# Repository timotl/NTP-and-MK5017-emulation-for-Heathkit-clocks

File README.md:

# NTP-and-MK5017-emulation-for-Heathkit-clocks
Documentation and modification of original clock to use ESP32 module instead of MK5017. 
Uses original chip socket and only requires 5v power module. 
No additional changes to the original hardware. 
Includes schematic and PCB for interface board. 
Full code and description of function. 
Documentation of the MK5017 

ESP32 sketch to replace MK5017AA and BA used in HeathKit panaplex clocks
Requires shift register and level shifting interface which connects to the original board via chip socket
No modifications to the original clock, except adding a 5v power supply module at the 120v input line
Heathkit GC-1092D, Heathkit GC-1005, Heathkit GC-1092A, Heathkit GC-1094 all fully tested
Display updates are state driven and writing to display is handled by hardware timer

WIFI mode:
Portal will be active if the configured wifi settings do not connect or if the time cannot be set from the configured NTP server after 1 minute.
NTP server, timezone, display off times are set through the portal.

ESP Touch (also snooze or alarmoff switches) changes display from Time to Date, Date to display off, display off to on.
GC-1092A/D - Original 555 touch hardware can be used, however each touch event must be at least 5 seconds apart.

MK5017 mode:
Switches and all behavior faithful to original hardware
RTC simulates battery backup of the GC-1092A/D (but works on all models) - Will consider time valid for configurable number of hours.
Note: some RTC modules don't keep time when powered off. Set BatteryBackup to 0 to disable holdover.
Switching modes will reset the model. Set model by pressing Hour/Month switch until the correct model is displayed, then toggle Time Set.

Switching modes:
Holding Hour/Month switch at power up will change between MK5017 and Wifi mode. Display will go from 888888 to ------ and restart

ArduinoOTA mode:
Alarm/Date switch also enters OTA mode. OTA mode uses AP mode with password and times out after 10 min.

Troubleshooting - Toggle Time Set switch 3x in under 5 seconds.
WIFI mode: Restart to portal to adjust WIFI and NTP settings.
MK5017 mode: Restart clearing RTC and model

Select ESP32-WROOM-DA Module in Arduino IDE
Partition scheme "Minimal SPIFFS (1.9MB APP with OTA/190KB SPIFFS) required if SerialBT is enabled

Also includes Manuals and other datasheets for the various models I can find.

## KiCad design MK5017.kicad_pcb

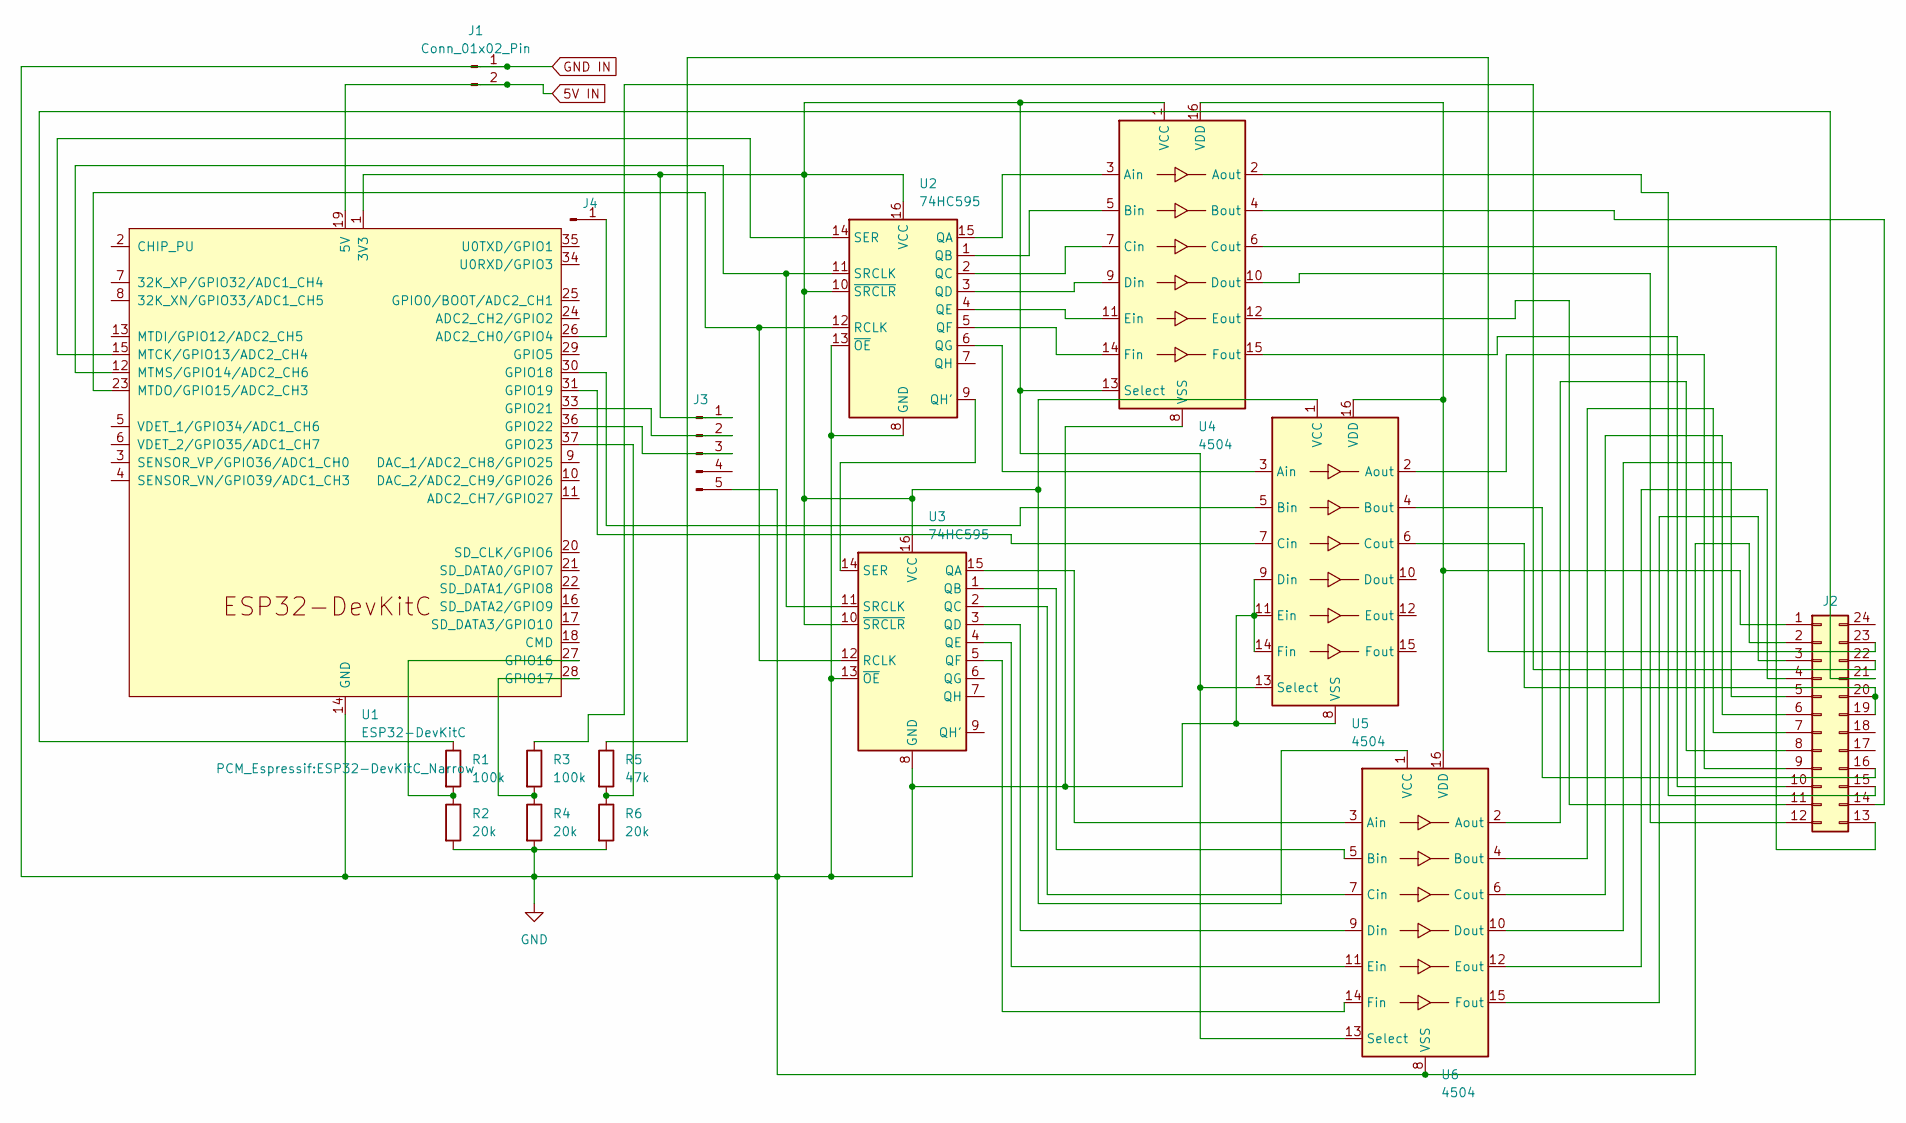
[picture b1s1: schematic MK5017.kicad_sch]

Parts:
J1: Conn_01x02_Pin; JST_EH_B2B-EH-A_1x02_P2.50mm_Vertical
J2: IDC-Header_2x12_P2.54mm_Vertical
J3: Conn_01x05_Pin; PinHeader_1x05_P2.54mm_Vertical
J4: Conn_01x01_Pin; PinHeader_1x01_P2.54mm_Vertical
R1, R3: 100k; R_0603_1608Metric
R2, R4, R6: 20k; R_0603_1608Metric
R5: 47k; R_0603_1608Metric
U1: ESP32-DevKitC; ESP32-DevKitC_Narrow
U2, U3: 74HC595; TSSOP-16_4.4x5mm_P0.65mm
U4, U5, U6: 4504; TSSOP-16_4.4x5mm_P0.65mm

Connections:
5V IN: J1.2, U1.19 (5V); also elsewhere on the board
GND IN: J1.1, J2.2, J3.5, R2.2, R4.2, R6.2, U1.14 (GND), U1.32 (GND), U1.38 (GND), U2.8 (GND), U2.13 (~OE), U3.8 (GND), U3.13 (~OE), U4.8 (VSS), U5.8 (VSS), U5.9 (Din), U5.11 (Ein), U5.14 (Fin), U6.8 (VSS); also elsewhere on the board
unnamed: J2.1, U4.16 (VDD), U5.16 (VDD), U6.16 (VDD)
unnamed: J2.3, U6.15 (Fout)
unnamed: J2.4, U6.12 (Eout)
unnamed: J2.5, U6.10 (Dout)
unnamed: J2.6, U6.6 (Cout)
unnamed: J2.7, U6.4 (Bout)
unnamed: J2.8, U6.2 (Aout)
unnamed: J2.9, U5.2 (Aout)
unnamed: J2.10, U4.15 (Fout)
unnamed: J2.11, U4.12 (Eout)
unnamed: J2.12, U4.10 (Dout)
unnamed: J2.13, U4.6 (Cout)
unnamed: J2.14, U4.4 (Bout)
unnamed: J2.15, U4.2 (Aout)
unnamed: J2.16, U5.4 (Bout)
unnamed: J2.19, J2.20, U5.6 (Cout)
unnamed: J2.21, R1.1
unnamed: J2.22, R3.1
unnamed: J2.23, R5.1
unnamed: J3.1, U1.1 (3V3), U2.10 (~SRCLR), U2.16 (VCC), U3.10 (~SRCLR), U3.16 (VCC), U4.1 (VCC), U4.13 (Select), U5.1 (VCC), U5.13 (Select), U6.1 (VCC), U6.13 (Select)
unnamed: J3.2, U1.33 (GPIO21)
unnamed: J3.3, U1.36 (GPIO22)
unnamed: J4.1, U1.26 (ADC2_CH0/GPIO4)
unnamed: R1.2, R2.1, U1.27 (GPIO16)
unnamed: R3.2, R4.1, U1.28 (GPIO17)
unnamed: U1.30 (GPIO18), U5.5 (Bin)
unnamed: U1.31 (GPIO19), U5.7 (Cin)
unnamed: R5.2, R6.1, U1.37 (GPIO23)
unnamed: U1.15 (MTCK/GPIO13/ADC2_CH4), U2.14 (SER)
unnamed: U1.23 (MTDO/GPIO15/ADC2_CH3), U2.12 (RCLK), U3.12 (RCLK)
unnamed: U1.12 (MTMS/GPIO14/ADC2_CH6), U2.11 (SRCLK), U3.11 (SRCLK)
unnamed: U2.15 (QA), U4.3 (Ain)
unnamed: U2.1 (QB), U4.5 (Bin)
unnamed: U2.2 (QC), U4.7 (Cin)
unnamed: U2.3 (QD), U4.9 (Din)
unnamed: U2.4 (QE), U4.11 (Ein)
unnamed: U2.5 (QF), U4.14 (Fin)
unnamed: U2.6 (QG), U5.3 (Ain)
unnamed: U2.9 (QH'), U3.14 (SER)
unnamed: U3.15 (QA), U6.3 (Ain)
unnamed: U3.1 (QB), U6.5 (Bin)
unnamed: U3.2 (QC), U6.7 (Cin)
unnamed: U3.3 (QD), U6.9 (Din)
unnamed: U3.4 (QE), U6.11 (Ein)
unnamed: U3.5 (QF), U6.14 (Fin)

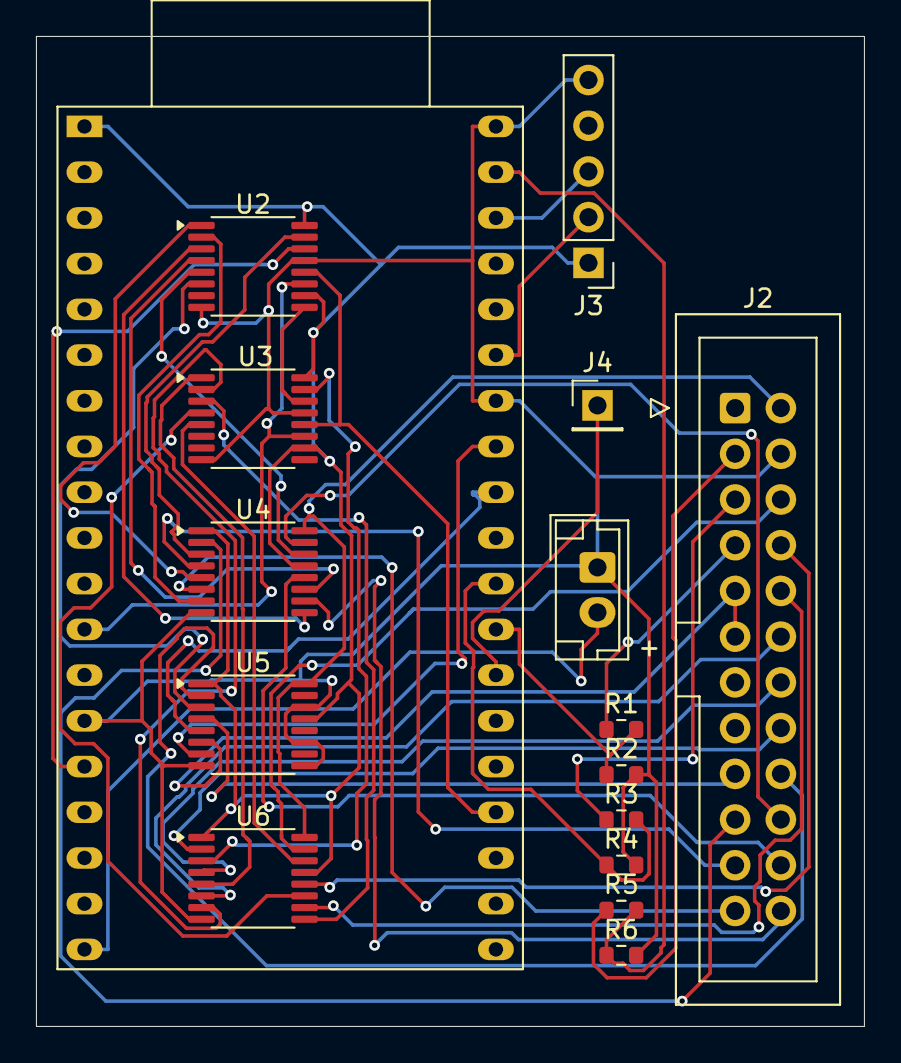
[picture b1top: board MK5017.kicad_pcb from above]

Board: 2 copper layers, 46.0 x 55.0 mm, 16 parts (0 on the bottom side), 47 nets.

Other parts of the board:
+: Conn_01x02_Pin; JST_EH_B2B-EH-A_1x02_P2.50mm_Vertical

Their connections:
5V IN: +.2; also elsewhere on the board
GND IN: +.1; also elsewhere on the board

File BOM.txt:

Parts:
ESP32 - any 38 pin module (NodeMCU etc)
Power supply https://www.digikey.com/en/products/detail/mean-well-usa-inc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

DIP plug https://www.digikey.com/en/products/detail/assmann-wsw-compo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
DS3231 module https://www.digikey.com/en/products/detail/seeed-technology-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
IDC socket and cable or directly solder ribbon.

U2, U3 HC595
U4,5,6 4504

R1 100k
R2 20k
R3 100k
R4 20k
R5 47k
R6 20k

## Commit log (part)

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2025-12-26 Update to fully support multiple MK5017 clocks
2025-12-26 KiCAD Schematic and PCB layout
2025-12-26 Update README with hardware and code details
    Clarify the documentation regarding hardware changes and code.
2025-12-26 Revise README title and project description
    Updated project title and description in README.
2026-06-14 Completed sketch for all models and modes
    Added configuration settings to portal.
2026-06-14 Interface board KiCad package
    Schematic and board layout with gerber files for interface board.
2026-06-15 Updated prefs defaults
